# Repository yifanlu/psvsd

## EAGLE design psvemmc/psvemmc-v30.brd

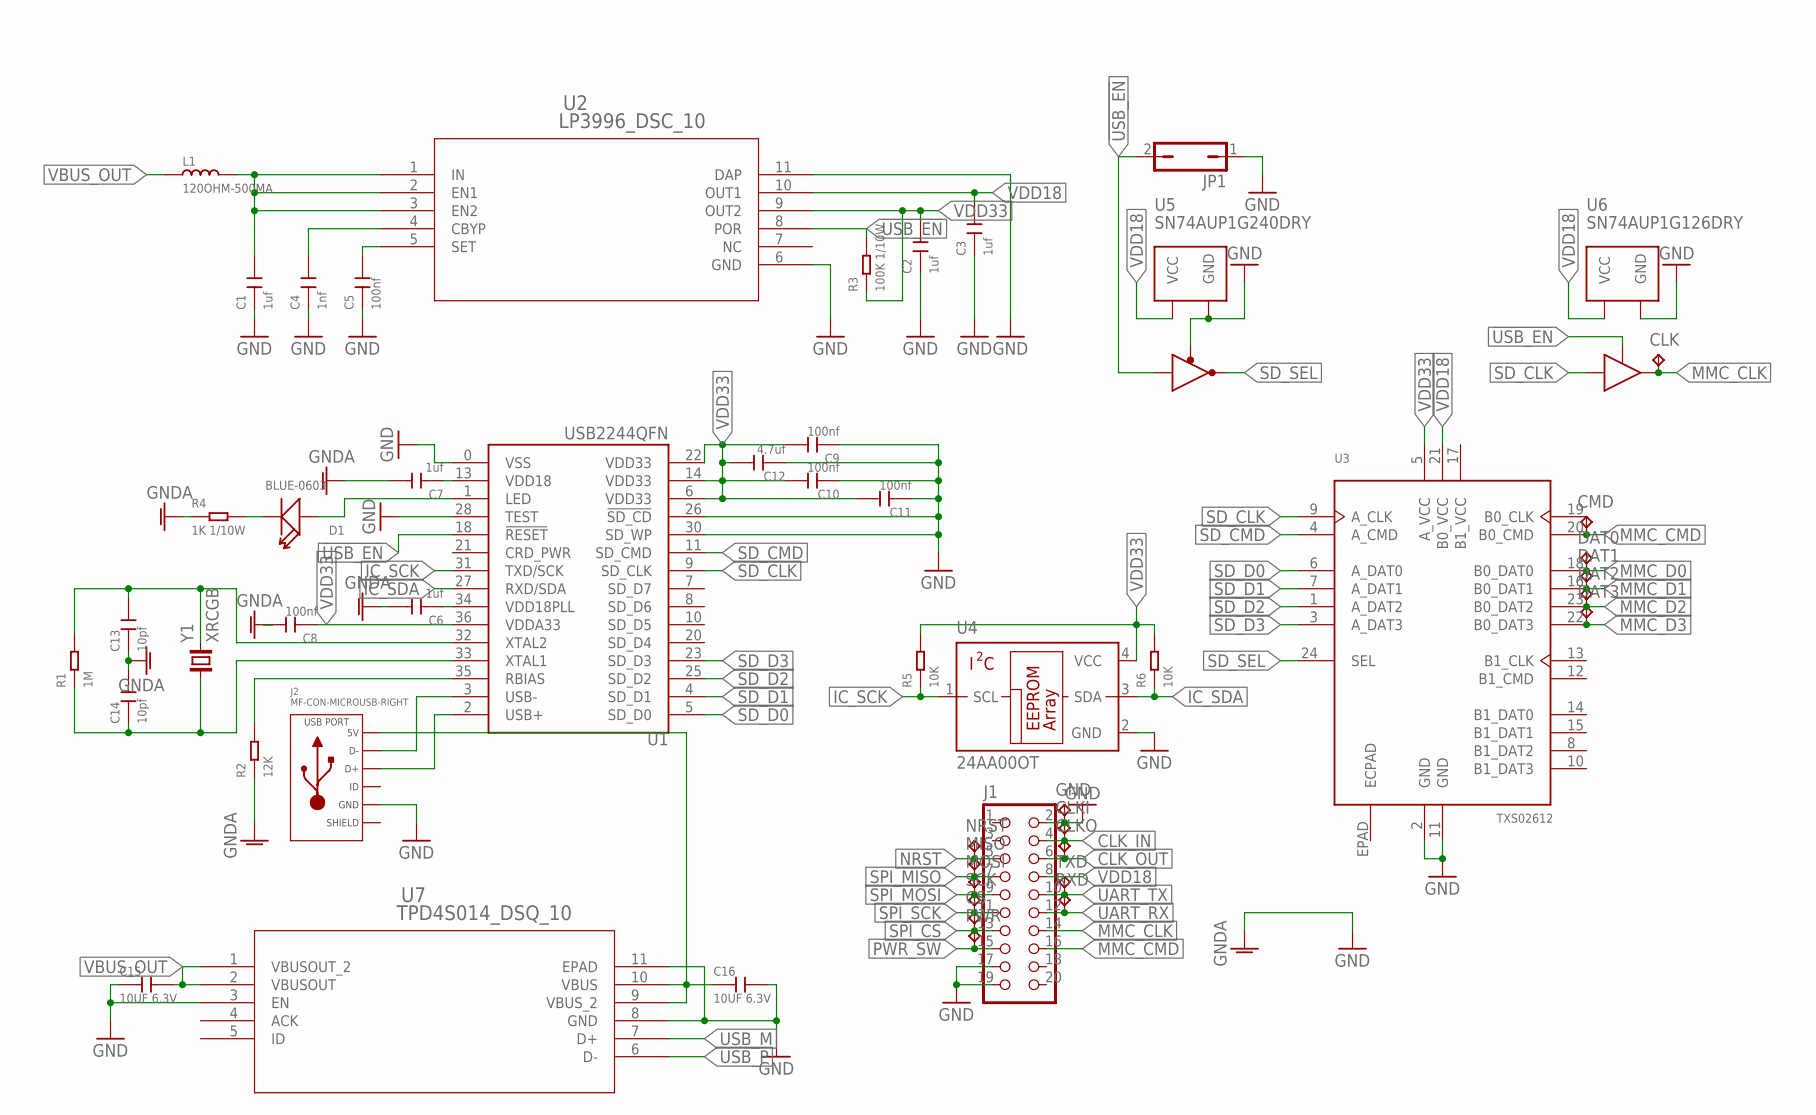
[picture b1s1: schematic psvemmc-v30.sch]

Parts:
C1, C2, C3, C6, C7: 1uf; C0603
C4: 1nf; C0603
C5, C8, C9, C10, C11: 100nf; C0603
C12: 4.7uf; C0603
C13, C14: 10pf; C0603
C15, C16: 10UF 6.3V; C0603
CLK: TPTP10R; TP10R
CLKI: TPTP10R; TP10R
CLKO: TPTP10R; TP10R
CMD: TPTP10R; TP10R
CS: TPTP10R; TP10R
D1: BLUE-0603; LED-0603
DAT0, DAT1, DAT2, DAT3: TPTP10R; TP10R
GND: TPTP10R; TP10R
J1: CON_HEADER_2X10-SHROUDED; PINSHRD_PTH_2X10
J2: MF-CON-MICROUSB-RIGHT; MICROUSB-RIGHT
JP1: JP1Q; JP1
L1: 120OHM-500MA; L0603
MISO: TPTP10R; TP10R
MOSI: TPTP10R; TP10R
NRST: TPTP10R; TP10R
PWR: TPTP10R; TP10R
R1: 1M; R0603
R2: 12K; R0603
R3: 100K 1/10W; R0603
R4: 1K 1/10W; R0603
R5, R6: 10K; R0603
RXD: TPTP10R; TP10R
SCK: TPTP10R; TP10R
TXD: TPTP10R; TP10R
U1: USB2244QFN; QFN36
U2: LP3996_DSC_10; SDA10A
U3: TXS02612; S-PWQFN-N24
U4: 24AA00OT; SOT23-5L
U5: SN74AUP1G240DRY; DRY6
U6: SN74AUP1G126DRY; DRY6
U7: TPD4S014_DSQ_10; DSQ10_1P5X0P9
Y1: XRCGB

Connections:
!USB_EN: JP1.2, R3.2, U1.18 (!RESET), U2.8 (POR), U5.2 (A), U6.1 (OE)
B1_VCC: U3.17 (B1_VCC)
CLK_IN: CLKI.TP, J1.4
CLK_OUT: CLKO.TP, J1.6
ECPAD: U3.EPAD (ECPAD)
GND: C1.1, C2.1, C3.1, C4.1, C5.1, C6.2, C7.2, C8.2, C9.1, C10.1, C11.1, C12.1, C13.1, C14.2, C15.1, C16.2, GND.TP, J1.2, J1.17, J1.19, J2.5 (GND), JP1.1, R2.1, R4.1, U1.0 (VSS), U1.26 (!SD_CD), U1.28 (TEST), U1.30 (SD_WP), U2.6 (GND), U2.11 (DAP), U3.2 (GND), U3.11 (GND), U4.2 (GND), U5.1 (!OE), U5.3 (GND), U6.3 (GND), U7.3 (EN), U7.8 (GND), U7.11 (EPAD)
IC_SCK: R5.1, U1.31 (TXD/SCK), U4.1 (SCL)
IC_SDA: R6.1, U1.27 (RXD/SDA), U4.3 (SDA)
LED: D1.+, U1.1 (LED)
LED_M: D1.-, R4.2
MMC_CLK: CLK.TP, J1.14, U6.4 (Y)
MMC_CMD: CMD.TP, J1.16, U3.20 (B0_CMD)
MMC_D0: DAT0.TP, U3.18 (B0_DAT0)
MMC_D1: DAT1.TP, U3.16 (B0_DAT1)
MMC_D2: DAT2.TP, U3.23 (B0_DAT2)
MMC_D3: DAT3.TP, U3.22 (B0_DAT3)
unnamed: C4.2, U2.4 (CBYP)
NRST: J1.5, NRST.TP
PWR_SW: J1.15, PWR.TP
RBIAS: R2.2, U1.35 (RBIAS)
SD_CLK: U1.9 (SD_CLK), U3.9 (A_CLK), U6.2 (A)
SD_CMD: U1.11 (SD_CMD), U3.4 (A_CMD)
SD_D0: U1.5 (SD_D0), U3.6 (A_DAT0)
SD_D1: U1.4 (SD_D1), U3.7 (A_DAT1)
SD_D2: U1.25 (SD_D2), U3.1 (A_DAT2)
SD_D3: U1.23 (SD_D3), U3.3 (A_DAT3)
SD_SEL: U3.24 (SEL), U5.4 (Y)
SET: C5.2, U2.5 (SET)
SLD: J2.S1 (SLD), J2.S2 (SLD), J2.S3 (SLD), J2.S4 (SLD), J2.S5 (SLD), J2.S6 (SLD)
SPI_CS: CS.TP, J1.13
SPI_MISO: J1.7, MISO.TP
SPI_MOSI: J1.9, MOSI.TP
SPI_SCK: J1.11, SCK.TP
UART_RX: J1.12, RXD.TP
UART_TX: J1.10, TXD.TP
USB_5V: C16.1, J2.1 (5V), U7.9 (VBUS_2), U7.10 (VBUS)
USB_M: J2.2 (D-), U1.3 (USB-), U7.7 (D+)
USB_P: J2.3 (D+), U1.2 (USB+), U7.6 (D-)
VBUS_OUT: C15.2, L1.1, U7.1 (VBUSOUT_2), U7.2 (VBUSOUT)
VDD5: C1.2, L1.2, U2.1 (IN), U2.2 (EN1), U2.3 (EN2)
VDD18: C3.2, J1.8, U2.10 (OUT1), U3.21 (B0_VCC), U5.6 (VCC), U6.6 (VCC)
VDD18_PLL: C6.1, U1.34 (VDD18PLL)
VDD18_USB: C7.1, U1.13 (VDD18)
VDD33: C2.2, C8.1, C9.2, C10.2, C11.2, C12.2, R3.1, R5.2, R6.2, U1.6 (VDD33), U1.14 (VDD33), U1.22 (VDD33), U1.36 (VDDA33), U2.9 (OUT2), U3.5 (A_VCC), U4.4 (VCC)
XTAL1: C14.1, R1.1, U1.33 (XTAL1), Y1.1
XTAL2: C13.2, R1.2, U1.32 (XTAL2), Y1.3 (2)

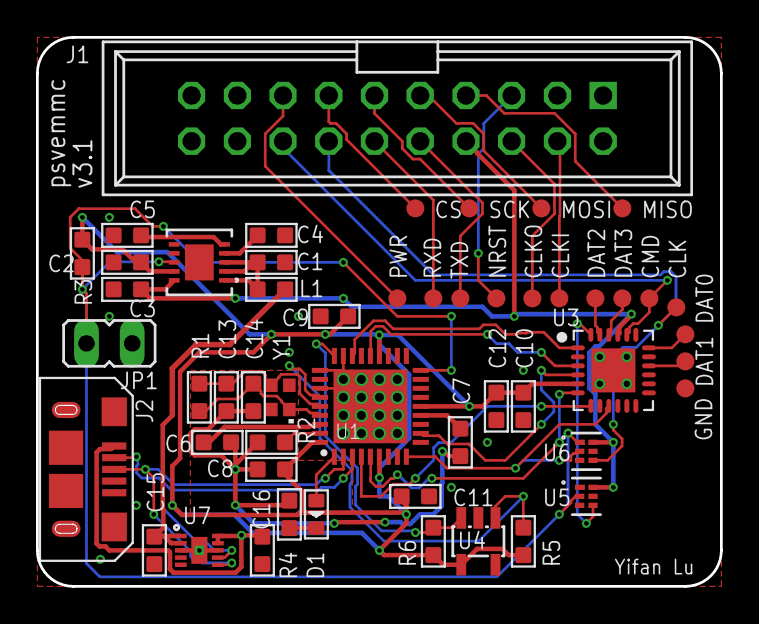
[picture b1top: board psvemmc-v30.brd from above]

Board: 2 copper layers, 38.0 x 30.5 mm, 52 parts (0 on the bottom side), 44 nets.

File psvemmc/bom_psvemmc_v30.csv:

Qty,Value,Device,Package,Parts
1,PINHD-2X5,Pin Header,2X05,JP1
1,100K,Resistor,0603,R3
5,100nF,Ceramic Capacitor,0603,"C5, C8, C9, C10, C11"
2,,Ferrite Bead,0603,"L1, L2"
1,12K,Resistor,0603,R2
1,1K,Resistor,0603,R4
1,1M,Resistor,0603,R1
1,10K,Resistor,0603,"R5, R6"
1,1nF,Ceramic Capacitor,0603,C4
5,1uF,Ceramic Capacitor Low ESR,0603,"C1, C2, C3, C6, C7"
1,4.7uF,Ceramic Capacitor Low ESR,0603,C12
2,10pF,Ceramic Capacitor,0603,"C13, C14"
2,10uF,Ceramic Capacitor,0603,"C15, C16"
1,BLUE,LED 0603,0603,D1
1,LP3996SD-1833/NOPB,"Texas Instruments LP3996 Dual LDO, 1.8V, 3.3V",WSON,U2
1,TXS02612RTWR,Texas Instruments TXS02612,RTW,U3
1,USB2244-AEZG-06,Microchip USB2244,QFN36,U1
1,XRCGB24M000F3N00R0,"Murata Hybrid Crystal, 24.000MHz, 30ppm, 6pF",XRCGB,Y1
1,10118193-0001LF,"FCI micro-USB port",,J2
1,24AA04T-I/OT,"Microchip 4K I2C EEPROM",SOT23-5,U4
1,SN74AUP1G240DRYR,"TI Low-Power Single Buffer/Driver with 3-State Output",SON,U5
1,SN74LVC1G125DRYR,"TI Low-Power Single Buffer/Driver with 3-State Output",SON,U6
1,TPD4S014DSQR,"TI USB Port Protection Device",WSON,U7

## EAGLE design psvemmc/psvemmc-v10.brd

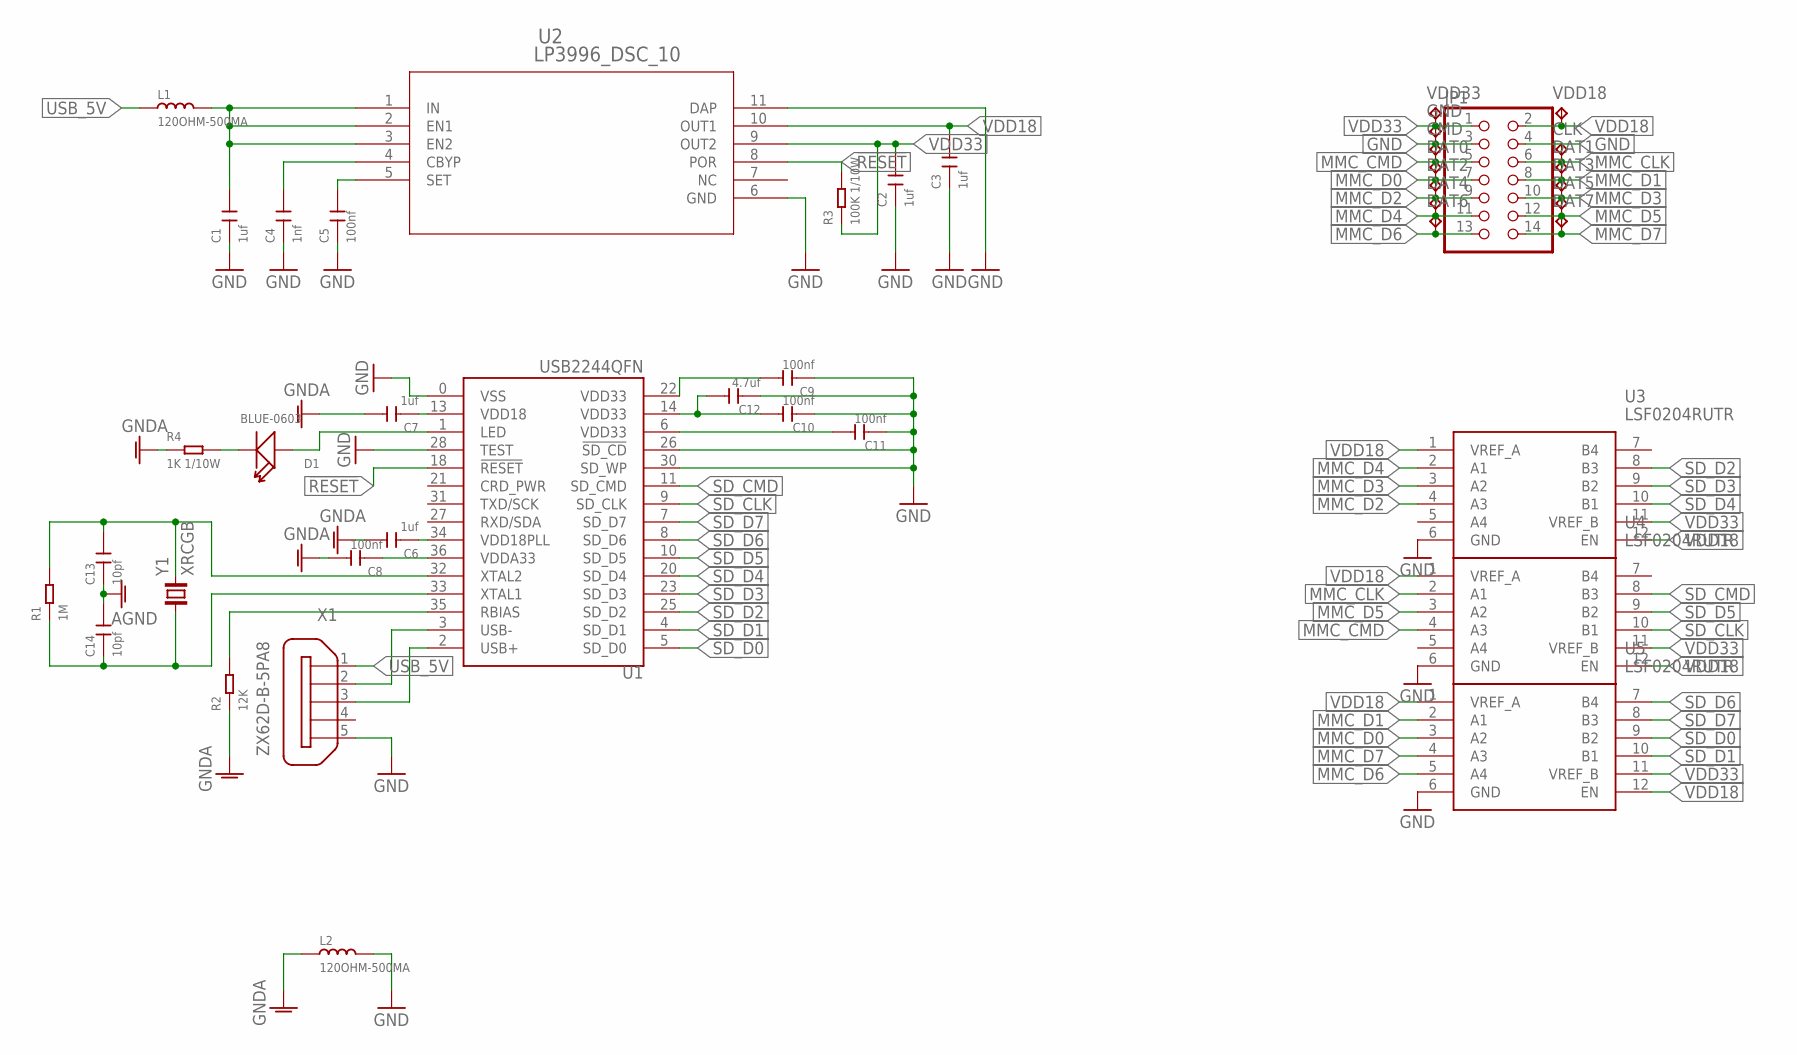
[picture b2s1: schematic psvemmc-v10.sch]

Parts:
C1, C2, C3, C6, C7: 1uf; C0603
C4: 1nf; C0603
C5, C8, C9, C10, C11: 100nf; C0603
C12: 4.7uf; C0603
C13, C14: 10pf; C0603
CLK: TPTP20SQ; TP20SQ
CMD: TPTP20SQ; TP20SQ
D1: BLUE-0603; LED-0603
DAT0, DAT1, DAT2, DAT3, DAT4, DAT5, DAT6, DAT7: TPTP20SQ; TP20SQ
GND: TPTP20SQ; TP20SQ
JP1: PINHD-2X7; 2X07
L1, L2: 120OHM-500MA; L0603
R1: 1M; R0603
R2: 12K; R0603
R3: 100K 1/10W; R0603
R4: 1K 1/10W; R0603
U1: USB2244QFN; QFN36
U2: LP3996_DSC_10; SDA10A
U3, U4, U5: LSF0204RUTR; RUT(R-PUQFN-N12)
VDD18, VDD33: TPTP20SQ; TP20SQ
X1: ZX62D-B-5PA8
Y1: XRCGB

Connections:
!RESET: R3.2, U1.18 (!RESET), U2.8 (POR)
GND: C1.1, C2.1, C3.1, C4.1, C5.1, C9.1, C10.1, C11.1, C12.1, GND.TP, JP1.3, JP1.4, L2.2, U1.0 (VSS), U1.26 (!SD_CD), U1.28 (TEST), U1.30 (SD_WP), U2.6 (GND), U2.11 (DAP), U3.6 (GND), U4.6 (GND), U5.6 (GND), X1.5
GNDA: C6.2, C7.2, C8.2, C13.1, C14.2, L2.1, R2.1, R4.1
LED: D1.+, U1.1 (LED)
LED_M: D1.-, R4.2
MMC_CLK: CLK.TP, JP1.6, U4.2 (A1)
MMC_CMD: CMD.TP, JP1.5, U4.4 (A3)
MMC_D0: DAT0.TP, JP1.7, U5.3 (A2)
MMC_D1: DAT1.TP, JP1.8, U5.2 (A1)
MMC_D2: DAT2.TP, JP1.9, U3.4 (A3)
MMC_D3: DAT3.TP, JP1.10, U3.3 (A2)
MMC_D4: DAT4.TP, JP1.11, U3.2 (A1)
MMC_D5: DAT5.TP, JP1.12, U4.3 (A2)
MMC_D6: DAT6.TP, JP1.13, U5.5 (A4)
MMC_D7: DAT7.TP, JP1.14, U5.4 (A3)
unnamed: C4.2, U2.4 (CBYP)
RBIAS: R2.2, U1.35 (RBIAS)
SD_CLK: U1.9 (SD_CLK), U4.10 (B1)
SD_CMD: U1.11 (SD_CMD), U4.8 (B3)
SD_D0: U1.5 (SD_D0), U5.9 (B2)
SD_D1: U1.4 (SD_D1), U5.10 (B1)
SD_D2: U1.25 (SD_D2), U3.8 (B3)
SD_D3: U1.23 (SD_D3), U3.9 (B2)
SD_D4: U1.20 (SD_D4), U3.10 (B1)
SD_D5: U1.10 (SD_D5), U4.9 (B2)
SD_D6: U1.8 (SD_D6), U5.7 (B4)
SD_D7: U1.7 (SD_D7), U5.8 (B3)
SET: C5.2, U2.5 (SET)
USB_5V: L1.1, X1.1
USB_M: U1.3 (USB-), X1.2
USB_P: U1.2 (USB+), X1.3
VDD5: C1.2, L1.2, U2.1 (IN), U2.2 (EN1), U2.3 (EN2)
VDD18: C3.2, JP1.2, U2.10 (OUT1), U3.1 (VREF_A), U3.12 (EN), U4.1 (VREF_A), U4.12 (EN), U5.1 (VREF_A), U5.12 (EN), VDD18.TP
VDD18_PLL: C6.1, U1.34 (VDD18PLL)
VDD18_USB: C7.1, U1.13 (VDD18)
VDD33: C2.2, C8.1, C9.2, C10.2, C11.2, C12.2, JP1.1, R3.1, U1.6 (VDD33), U1.14 (VDD33), U1.22 (VDD33), U1.36 (VDDA33), U2.9 (OUT2), U3.11 (VREF_B), U4.11 (VREF_B), U5.11 (VREF_B), VDD33.TP
XTAL1: C14.1, R1.1, U1.33 (XTAL1), Y1.1
XTAL2: C13.2, R1.2, U1.32 (XTAL2), Y1.3 (2)

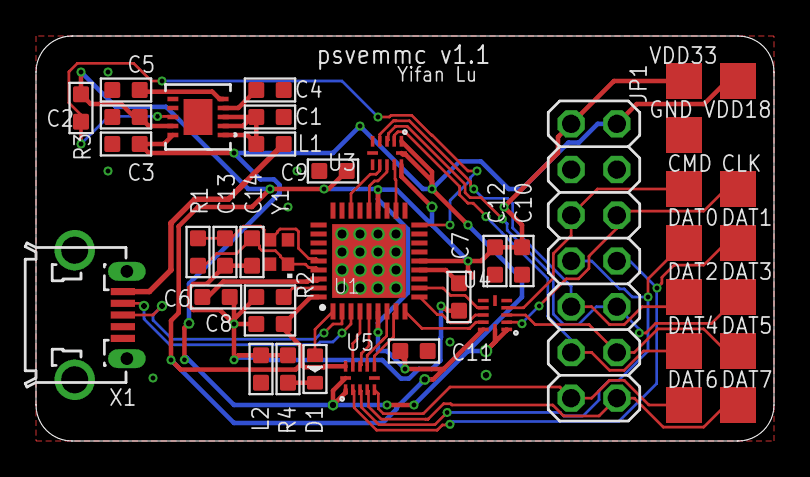
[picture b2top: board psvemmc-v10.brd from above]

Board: 2 copper layers, 41.0 x 22.5 mm, 42 parts (0 on the bottom side), 38 nets.

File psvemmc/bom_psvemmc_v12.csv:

Qty,Value,Device,Package,Parts
1,PINHD-2X5,Pin Header,2X05,JP1
1,100K,Resistor,0603,R3
5,100nF,Ceramic Capacitor,0603,"C5, C8, C9, C10, C11"
2,,Ferrite Bead,0603,"L1, L2"
1,12K,Resistor,0603,R2
1,1K,Resistor,0603,R4
1,1M,Resistor,0603,R1
1,1nF,Ceramic Capacitor,0603,C4
5,1uF,Ceramic Capacitor Low ESR,0603,"C1, C2, C3, C6, C7"
1,4.7uF,Ceramic Capacitor Low ESR,0603,C12
2,10pF,Ceramic Capacitor,0603,"C13, C14"
1,BLUE,LED 0603,0603,D1
1,LP3996SD-1833/NOPB,"Texas Instruments LP3996 Dual LDO, 1.8V, 3.3V",WSON,U2
1,TXS02612RTWR,Texas Instruments TXS02612,RTW,U3
1,USB2244-AEZG-06,Microchip USB2244,QFN36,U1
1,XRCGB24M000F3N00R0,"Murata Hybrid Crystal, 24.000MHz, 30ppm, 6pF",XRCGB,Y1
1,,"Micro USB Type AB receptacle, through hole",,X1

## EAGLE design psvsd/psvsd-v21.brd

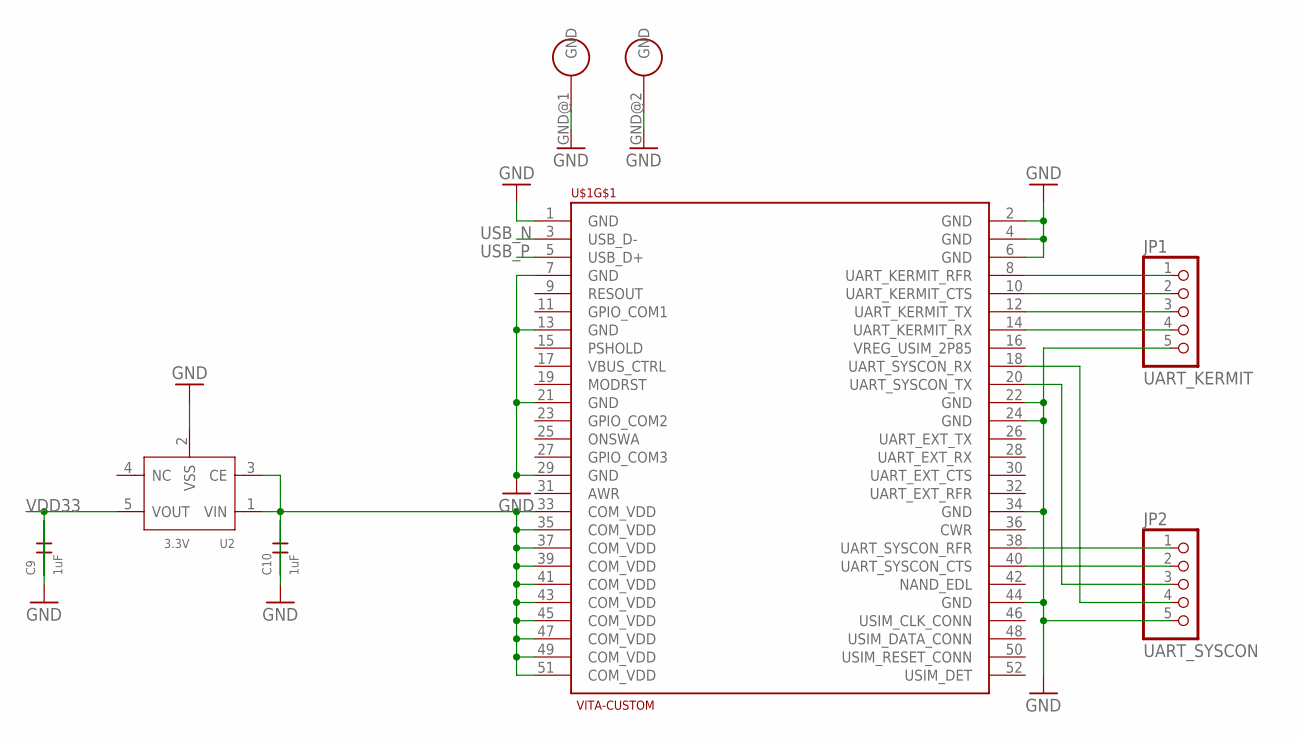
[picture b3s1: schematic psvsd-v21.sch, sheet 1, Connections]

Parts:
C9, C10: 1uF; C0603
JP1: UART_KERMIT; 1X05
JP2: UART_SYSCON; 1X05
U2: 3.3V; SOT-23-5
U$1: VITA-CUSTOM; VITA-MINI-PCI-E

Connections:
GND: C9.2, C10.2, JP1.5, JP2.5, U2.2 (VSS), U$1.1 (GND), U$1.2 (GND), U$1.4 (GND), U$1.6 (GND), U$1.7 (GND), U$1.13 (GND), U$1.21 (GND), U$1.22 (GND), U$1.24 (GND), U$1.29 (GND), U$1.34 (GND), U$1.44 (GND), U$1.GND@1 (GND), U$1.GND@2 (GND); also elsewhere on the board
UART_KERMIT_CTS: JP1.2, U$1.10 (UART_KERMIT_CTS)
UART_KERMIT_RFR: JP1.1, U$1.8 (UART_KERMIT_RFR)
UART_KERMIT_RX: JP1.4, U$1.14 (UART_KERMIT_RX)
UART_KERMIT_TX: JP1.3, U$1.12 (UART_KERMIT_TX)
UART_SYSCON_CTS: JP2.2, U$1.40 (UART_SYSCON_CTS)
UART_SYSCON_RFR: JP2.1, U$1.38 (UART_SYSCON_RFR)
UART_SYSCON_RX: JP2.4, U$1.18 (UART_SYSCON_RX)
UART_SYSCON_TX: JP2.3, U$1.20 (UART_SYSCON_TX)
USB_N: U$1.3 (USB_D-); also elsewhere on the board
USB_P: U$1.5 (USB_D+); also elsewhere on the board
VDD: C10.1, U2.1 (VIN), U2.3 (CE), U$1.33 (COM_VDD), U$1.35 (COM_VDD), U$1.37 (COM_VDD), U$1.39 (COM_VDD), U$1.41 (COM_VDD), U$1.43 (COM_VDD), U$1.45 (COM_VDD), U$1.47 (COM_VDD), U$1.49 (COM_VDD), U$1.51 (COM_VDD)
VDD33: C9.1, U2.5 (VOUT); also elsewhere on the board

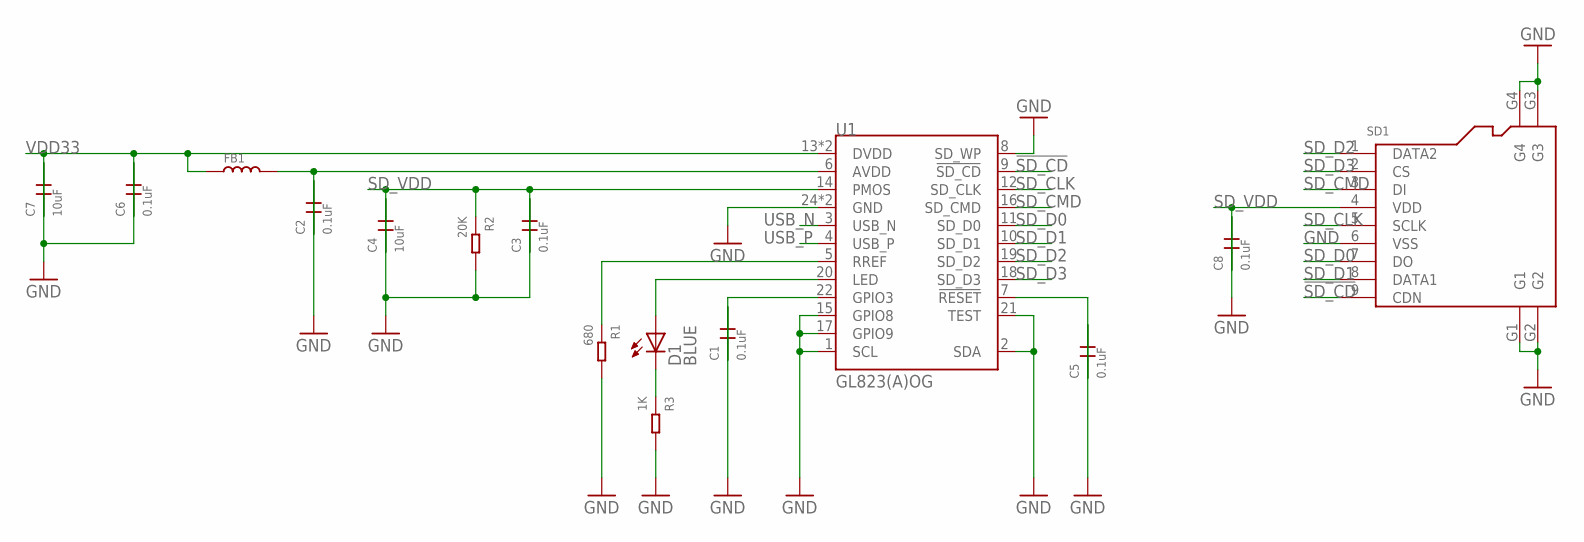
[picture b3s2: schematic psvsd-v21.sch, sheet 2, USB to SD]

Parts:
C1, C2, C3, C5, C6, C8: 0.1uF; C0603
C4, C7: 10uF; C0603
D1: BLUE; CHIP-LED0603
FB1: SMD-FERRITE-BEAD-2500R-50MA(0603); L0603
R1: 680; R0603
R2: 20K; R0603
R3: 1K; R0603
SD1: MICRO-SD-CARD-SOCKET-9P(ST-TF-003A); MICRO-SD9+4P-SMD-16.1X14.5X1.85MM
U1: GL823(A)OG; QFN-24

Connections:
!RESET: C5.1, U1.7 (!RESET)
!SD_CD: SD1.9 (CDN), U1.9 (!SD_CD)
AVDD33: C2.1, FB1.2, U1.6 (AVDD)
GND: C1.2, C2.2, C3.2, C4.2, C5.2, C6.2, C7.2, C8.2, R1.2, R2.2, R3.2, SD1.6 (VSS), SD1.G1, SD1.G2, SD1.G3, SD1.G4, U1.1 (SCL), U1.2 (SDA), U1.8 (SD_WP), U1.15 (GPIO8), U1.17 (GPIO9), U1.21 (TEST), U1.24 (GND), U1.25 (GND); also elsewhere on the board
GPIO3: C1.1, U1.22 (GPIO3)
LED: D1.A, U1.20 (LED)
LED_N: D1.C, R3.1
RREF: R1.1, U1.5 (RREF)
SD_CLK: SD1.5 (SCLK), U1.12 (SD_CLK)
SD_CMD: SD1.3 (DI), U1.16 (SD_CMD)
SD_D0: SD1.7 (DO), U1.11 (SD_D0)
SD_D1: SD1.8 (DATA1), U1.10 (SD_D1)
SD_D2: SD1.1 (DATA2), U1.19 (SD_D2)
SD_D3: SD1.2 (CS), U1.18 (SD_D3)
SD_VDD: C3.1, C4.1, C8.1, R2.1, SD1.4 (VDD), U1.14 (PMOS)
USB_N: U1.3 (USB_N); also elsewhere on the board
USB_P: U1.4 (USB_P); also elsewhere on the board
VDD33: C6.1, C7.1, FB1.1, U1.13 (DVDD), U1.23 (DVDD); also elsewhere on the board

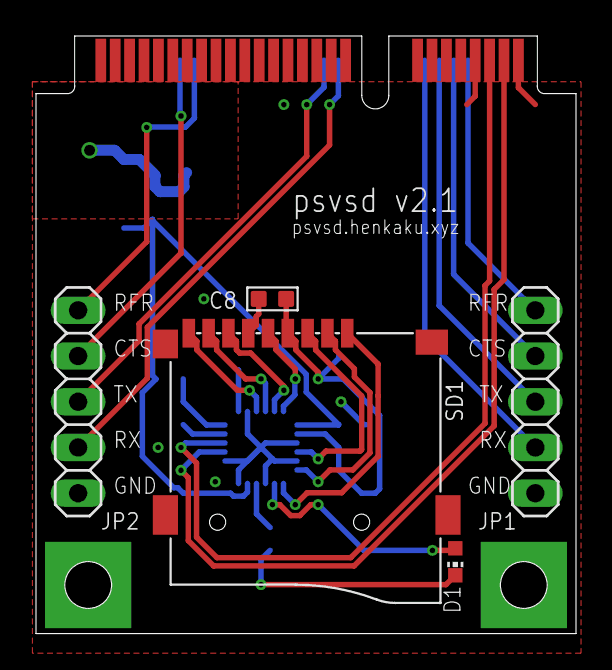
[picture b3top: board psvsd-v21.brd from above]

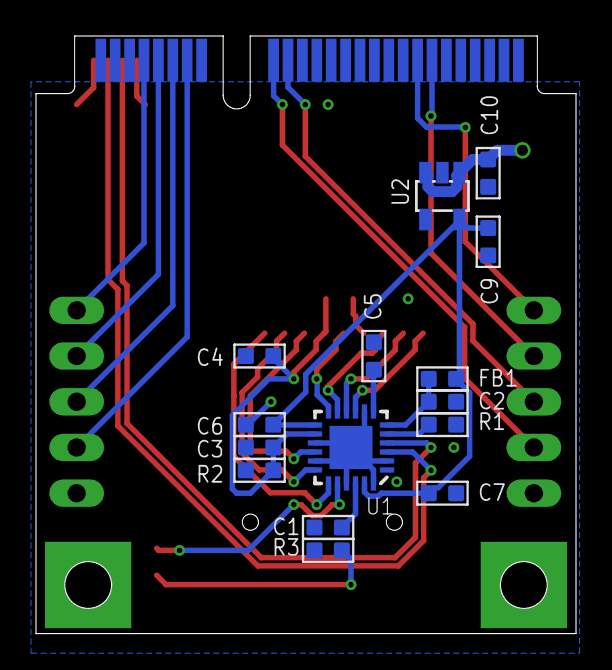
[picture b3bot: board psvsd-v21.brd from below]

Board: 2 copper layers, 30.0 x 33.2 mm, 21 parts (15 on the bottom side), 27 nets.

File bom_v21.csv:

Qty,Reference,Description,Manufacturer,Part,Notes
6,"C1,C2,C3,C5,C6,C8","Capacitor, 0.1uF, 0603",Yageo,CC0603KRX7R9BB104,
2,"C4,C7","Capacitor, 10uF, 0603",Murata,GRM188R60J106ME47D,
2,"C9,C10","Capacitor, 1.0uF, 0603",Yageo,CC0603KRX7R8BB105,
1,FB1,"Ferrite Bead, 120 Ohm @ 100MHz, 0603",Murata,BLM18TG121TN1D,
1,SD1,SMD Micro SD Card Socket,Best,TF-01,
2,"JP1,JP2","Pin Headers 0.1” spacing, 5",,,Only fill if needed
1,R1,"Resistor, 680, 0603",Yageo,RC0603JR-07680RL,
1,R2,"Resistor, 20K, 0603",Yageo,RC0603FR-0720KL,
1,R3,"Resistor, 1K, 0603",Yageo,RC0603JR-071KL,
1,D1,"LED Blue, 3.2V, 20mA, 0603",Everlight,19-217-BHC-ZL1M2RY-3T,
1,U2,"LDO 3.3V, 200mA",Micrel,MIC5504-3.3YM5-TR,
1,U1,GL823 3.3V QFN24,Genesys,GL823,

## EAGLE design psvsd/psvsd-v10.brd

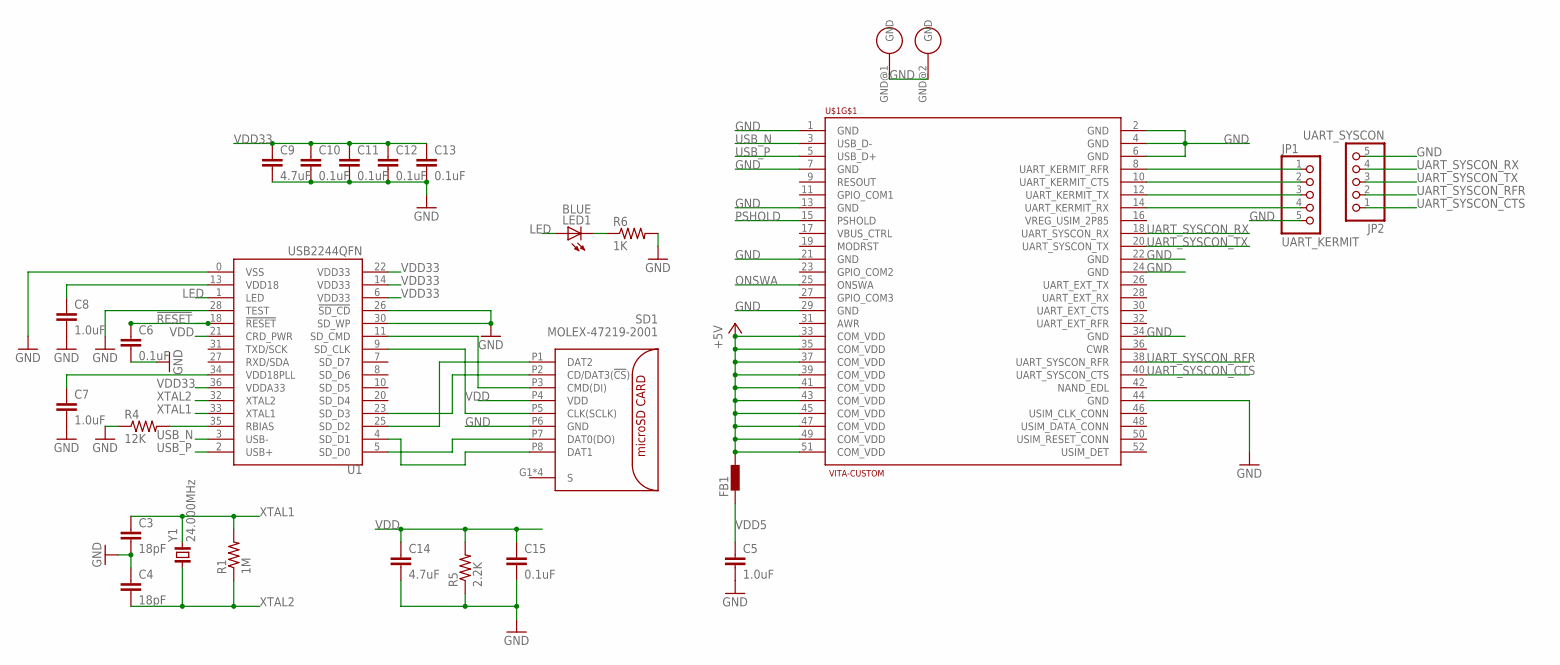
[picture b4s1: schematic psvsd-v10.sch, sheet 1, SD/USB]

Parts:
C3, C4: 18pF; C0402
C5, C7, C8: 1.0uF; C0603
C6, C10, C11, C12, C13, C15: 0.1uF; C0402
C9, C14: 4.7uF; C0603
FB1: BLM15HB121SN1; 0402
JP1: UART_KERMIT; 1X05
JP2: UART_SYSCON; 1X05
LED1: BLUE; SML0603
R1: 1M; R0603
R4: 12K; R0603
R5: 2.2K; R0603
R6: 1K; R0603
SD1: MOLEX-47219-2001; MOLEX:47219-2001
U1: USB2244QFN; QFN36
U$1: VITA-CUSTOM; VITA-MINI-PCI-E
Y1: 24.000MHz; XRCGB

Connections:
!RESET: C6.1, U1.18 (!RESET); also elsewhere on the board
+5V: FB1.2, U$1.33 (COM_VDD), U$1.35 (COM_VDD), U$1.37 (COM_VDD), U$1.39 (COM_VDD), U$1.41 (COM_VDD), U$1.43 (COM_VDD), U$1.45 (COM_VDD), U$1.47 (COM_VDD), U$1.49 (COM_VDD), U$1.51 (COM_VDD)
GND: C3.2, C4.1, C5.2, C6.2, C7.2, C8.2, C9.2, C10.2, C11.2, C12.2, C13.2, C14.2, C15.2, JP1.5, JP2.5, R4.1, R5.1, R6.2, SD1.P6 (GND), U1.0 (VSS), U1.26 (!SD_CD), U1.28 (TEST), U1.30 (SD_WP), U$1.1 (GND), U$1.2 (GND), U$1.4 (GND), U$1.6 (GND), U$1.7 (GND), U$1.13 (GND), U$1.21 (GND), U$1.22 (GND), U$1.24 (GND), U$1.29 (GND), U$1.34 (GND), U$1.44 (GND), U$1.GND@1 (GND), U$1.GND@2 (GND); also elsewhere on the board
LED: LED1.A, U1.1 (LED)
unnamed: LED1.C, R6.1
ONSWA: U$1.25 (ONSWA); also elsewhere on the board
PSHOLD: U$1.15 (PSHOLD); also elsewhere on the board
RBIAS: R4.2, U1.35 (RBIAS)
SD_CLK: SD1.P5 (CLK(SCLK)), U1.9 (SD_CLK)
SD_CMD: SD1.P3 (CMD(DI)), U1.11 (SD_CMD)
SD_D0: SD1.P7 (DAT0(DO)), U1.5 (SD_D0)
SD_D1: SD1.P8 (DAT1), U1.4 (SD_D1)
SD_D2: SD1.P1 (DAT2), U1.25 (SD_D2)
SD_D3: SD1.P2 (CD/DAT3(!CS!)), U1.23 (SD_D3)
UART_KERMIT_CTS: JP1.2, U$1.10 (UART_KERMIT_CTS)
UART_KERMIT_RFR: JP1.1, U$1.8 (UART_KERMIT_RFR)
UART_KERMIT_RX: JP1.4, U$1.14 (UART_KERMIT_RX)
UART_KERMIT_TX: JP1.3, U$1.12 (UART_KERMIT_TX)
UART_SYSCON_CTS: JP2.1, U$1.40 (UART_SYSCON_CTS)
UART_SYSCON_RFR: JP2.2, U$1.38 (UART_SYSCON_RFR)
UART_SYSCON_RX: JP2.4, U$1.18 (UART_SYSCON_RX)
UART_SYSCON_TX: JP2.3, U$1.20 (UART_SYSCON_TX)
USBVDD18: C8.1, U1.13 (VDD18)
USBVDD18PLL: C7.1, U1.34 (VDD18PLL)
USB_N: U1.3 (USB-), U$1.3 (USB_D-)
USB_P: U1.2 (USB+), U$1.5 (USB_D+)
VDD: C14.1, C15.1, R5.2, SD1.P4 (VDD), U1.21 (CRD_PWR)
VDD5: C5.1, FB1.1; also elsewhere on the board
VDD33: C9.1, C10.1, C11.1, C12.1, C13.1, U1.6 (VDD33), U1.14 (VDD33), U1.22 (VDD33), U1.36 (VDDA33); also elsewhere on the board
XTAL1: C3.1, R1.2, U1.33 (XTAL1), Y1.3 (2)
XTAL2: C4.2, R1.1, U1.32 (XTAL2), Y1.1

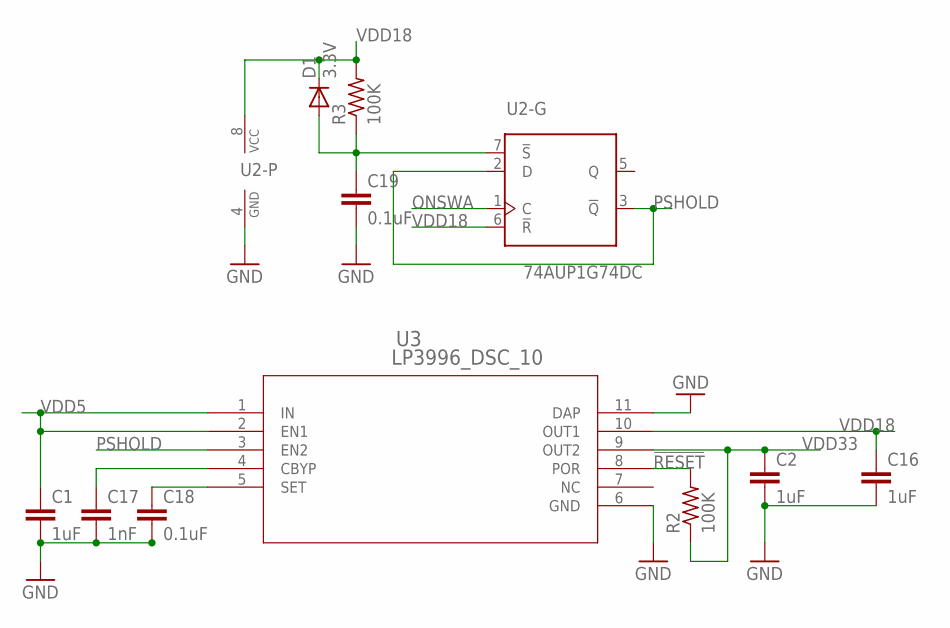
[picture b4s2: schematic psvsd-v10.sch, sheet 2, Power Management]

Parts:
C1, C2, C16: 1uF; C0603
C17: 1nF; C0402
C18, C19: 0.1uF; C0402
D1: 3.3V; SOD523
R2, R3: 100K; R0603
U2: 74AUP1G74DC; SOT765
U3: LP3996_DSC_10; SDA10A

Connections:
!RESET: R2.2, U3.8 (POR); also elsewhere on the board
!S: C19.1, D1.A, R3.1, U2.7 (!S)
CBYP: C17.1, U3.4 (CBYP)
CSET: C18.1, U3.5 (SET)
GND: C1.2, C2.2, C16.2, C17.2, C18.2, C19.2, U2.4 (GND), U3.6 (GND), U3.11 (DAP); also elsewhere on the board
ONSWA: U2.1 (C); also elsewhere on the board
PSHOLD: U2.2 (D), U2.3 (!Q), U3.3 (EN2); also elsewhere on the board
VDD5: C1.1, U3.1 (IN), U3.2 (EN1); also elsewhere on the board
VDD18: C16.1, D1.C, R3.2, U2.6 (!R), U2.8 (VCC), U3.10 (OUT1)
VDD33: C2.1, R2.1, U3.9 (OUT2); also elsewhere on the board

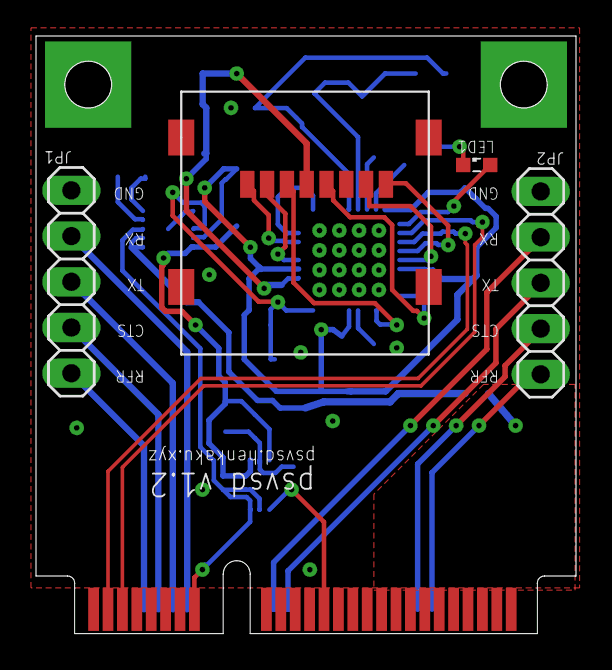
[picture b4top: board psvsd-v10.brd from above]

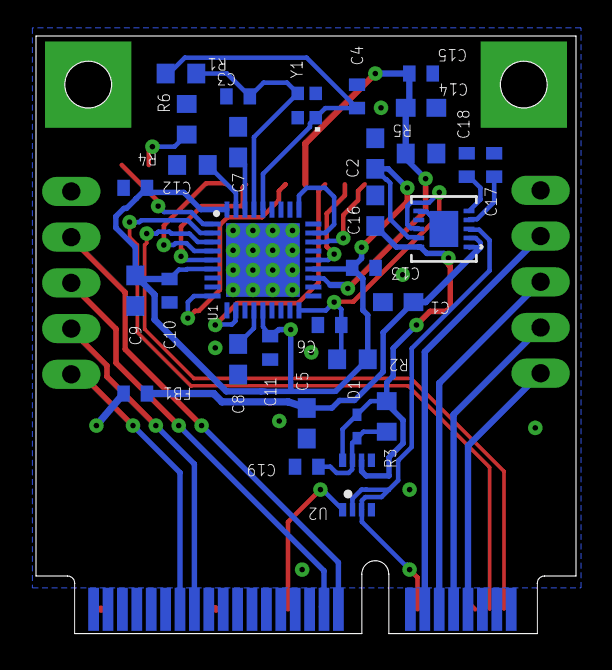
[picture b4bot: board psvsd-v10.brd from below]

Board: 2 copper layers, 30.0 x 33.2 mm, 36 parts (31 on the bottom side), 35 nets.

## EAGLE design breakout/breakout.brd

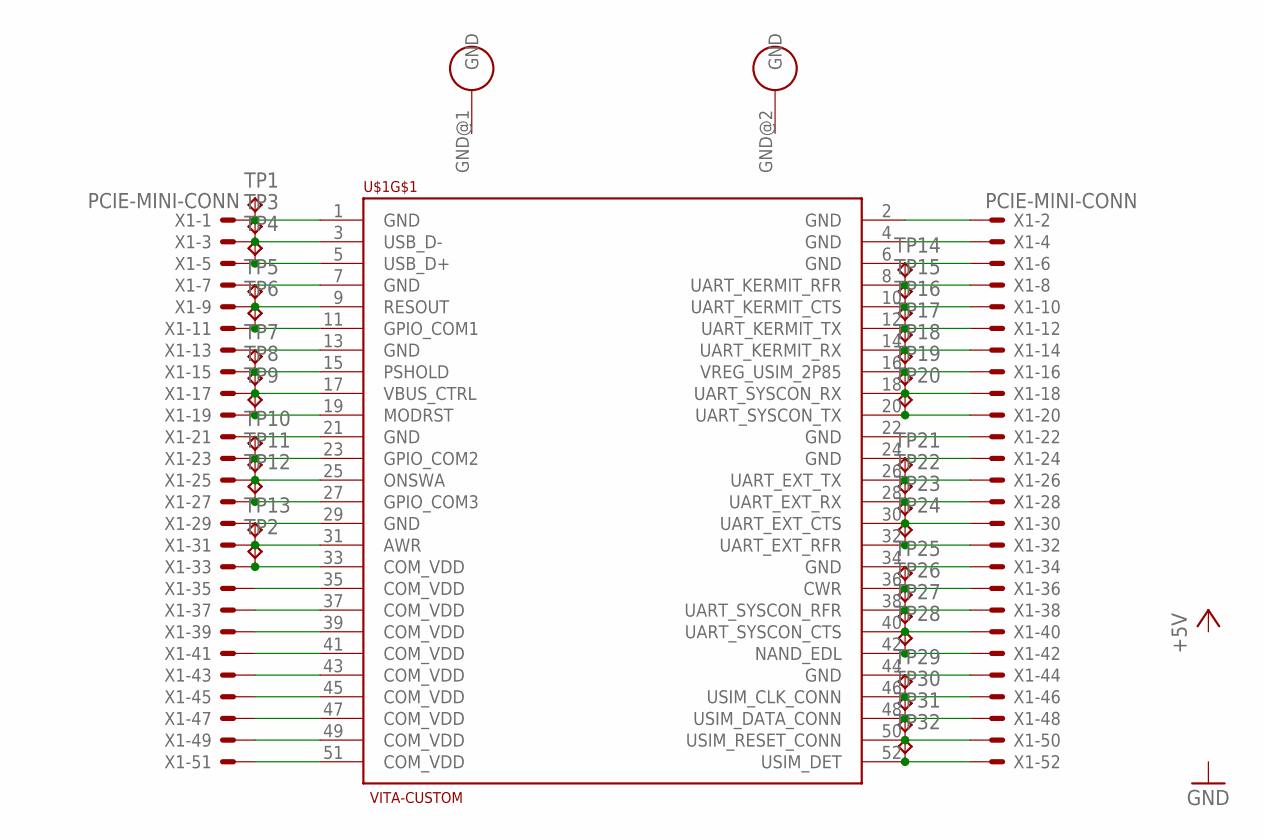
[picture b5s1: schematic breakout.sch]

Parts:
TP1, TP2, TP3, TP4, TP5, TP6, TP7, TP8, TP9, TP10, TP11, TP12, TP13, TP14, TP15, TP16, TP17, TP18, TP19, TP20, TP21, TP22, TP23, TP24, TP25, TP26, TP27, TP28, TP29, TP30, TP31, TP32: TPTP20R; TP20R
U$1: VITA-CUSTOM; VITA-MINI-PCI-E
X1: PCIE-MINI-CONN

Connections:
+5V: TP2.TP, U$1.33 (COM_VDD), U$1.35 (COM_VDD), U$1.37 (COM_VDD), U$1.39 (COM_VDD), U$1.41 (COM_VDD), U$1.43 (COM_VDD), U$1.45 (COM_VDD), U$1.47 (COM_VDD), U$1.49 (COM_VDD), U$1.51 (COM_VDD), X1.33, X1.35, X1.37, X1.39, X1.41, X1.43, X1.45, X1.47, X1.49, X1.51
AWR: TP13.TP, U$1.31 (AWR), X1.31
CWR: TP25.TP, U$1.36 (CWR), X1.36
GND: TP1.TP, U$1.1 (GND), U$1.2 (GND), U$1.4 (GND), U$1.6 (GND), U$1.7 (GND), U$1.13 (GND), U$1.21 (GND), U$1.22 (GND), U$1.24 (GND), U$1.29 (GND), U$1.34 (GND), U$1.44 (GND), U$1.GND@1 (GND), U$1.GND@2 (GND), X1.1, X1.2, X1.4, X1.6, X1.7, X1.13, X1.21, X1.22, X1.24, X1.29, X1.34, X1.44
GPIO_COM1: TP6.TP, U$1.11 (GPIO_COM1), X1.11
GPIO_COM2: TP10.TP, U$1.23 (GPIO_COM2), X1.23
GPIO_COM3: TP12.TP, U$1.27 (GPIO_COM3), X1.27
MODRST: TP9.TP, U$1.19 (MODRST), X1.19
NAND_EDL: TP28.TP, U$1.42 (NAND_EDL), X1.42
ONSWA: TP11.TP, U$1.25 (ONSWA), X1.25
PSHOLD: TP7.TP, U$1.15 (PSHOLD), X1.15
RESOUT: TP5.TP, U$1.9 (RESOUT), X1.9
UART_EXT_CTS: TP23.TP, U$1.30 (UART_EXT_CTS), X1.30
UART_EXT_RFR: TP24.TP, U$1.32 (UART_EXT_RFR), X1.32
UART_EXT_RX: TP22.TP, U$1.28 (UART_EXT_RX), X1.28
UART_EXT_TX: TP21.TP, U$1.26 (UART_EXT_TX), X1.26
UART_KERMIT_CTS: TP15.TP, U$1.10 (UART_KERMIT_CTS), X1.10
UART_KERMIT_RFR: TP14.TP, U$1.8 (UART_KERMIT_RFR), X1.8
UART_KERMIT_RX: TP17.TP, U$1.14 (UART_KERMIT_RX), X1.14
UART_KERMIT_TX: TP16.TP, U$1.12 (UART_KERMIT_TX), X1.12
UART_SYSCON_CTS: TP27.TP, U$1.40 (UART_SYSCON_CTS), X1.40
UART_SYSCON_RFR: TP26.TP, U$1.38 (UART_SYSCON_RFR), X1.38
UART_SYSCON_RX: TP19.TP, U$1.18 (UART_SYSCON_RX), X1.18
UART_SYSCON_TX: TP20.TP, U$1.20 (UART_SYSCON_TX), X1.20
USB_N: TP3.TP, U$1.3 (USB_D-), X1.3
USB_P: TP4.TP, U$1.5 (USB_D+), X1.5
USIM_CLK_CONN: TP29.TP, U$1.46 (USIM_CLK_CONN), X1.46
USIM_DATA_CONN: TP30.TP, U$1.48 (USIM_DATA_CONN), X1.48
USIM_DET: TP32.TP, U$1.52 (USIM_DET), X1.52
USIM_RESET_CONN: TP31.TP, U$1.50 (USIM_RESET_CONN), X1.50
VBUS_CTRL: TP8.TP, U$1.17 (VBUS_CTRL), X1.17
VREG_USIM_2P85: TP18.TP, U$1.16 (VREG_USIM_2P85), X1.16

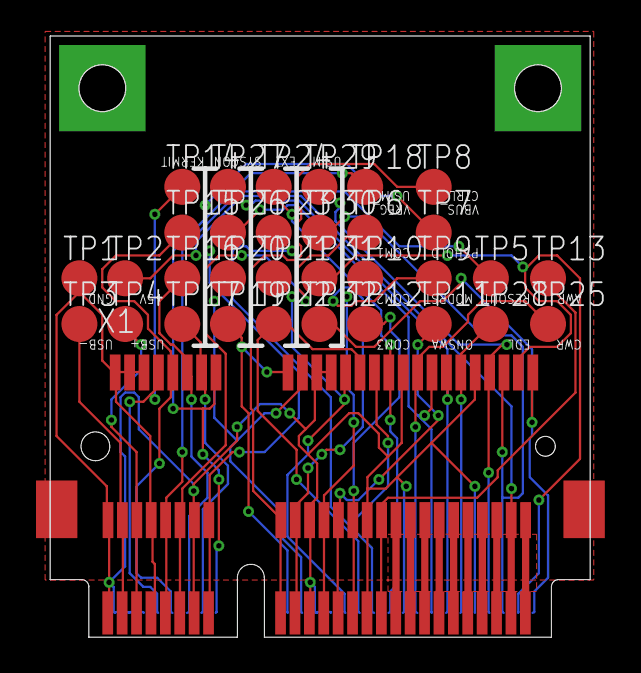
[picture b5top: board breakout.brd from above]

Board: 2 copper layers, 30.0 x 33.4 mm, 34 parts (0 on the bottom side), 32 nets.

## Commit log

2017-04-21 Initial commit.
2017-04-25 DRC fixes
2017-04-25 More cleanups
2017-04-25 Fixed dimensions
2017-04-25 Name/value layout in bottom layer
2017-04-25 Added forgotten tStop layer to USB2244 chip
2017-04-25 Moved some labels away from vias
2017-04-25 Added BOM
2017-04-26 Added breakout board
2017-04-26 Removed molex mark from silkscreen
2017-04-26 Better routing of the +5V pins to handle large currents
2017-04-26 Corrected wrong pins for USB+/USB-
2017-04-26 Fix incorrect signal in breakout board
2017-04-26 Fixed USB+/USB- signal in psvsd
2017-04-26 Fixed DRC for new USB lines placement
2017-04-27 Added new hinge-type microsd connector
2017-05-18 Added LED indicator
2017-05-19 Added Vita PCIe form factor
2017-05-19 Updated board to be right size
2017-05-19 Really size the vita card correctly now
2017-05-19 Resize both boards
2017-05-19 Shifted all components up in the new space
2017-05-19 Extended ground plane on top layer to even electric properties
2017-05-20 Replaced microSD connector with cheaper part
2017-05-20 Added value for LED
2017-05-20 Removed unneedeed lbr for hinge type molex connector
2017-05-24 Moved some labels in the silkscreen to prevent being cut off
2017-05-26 Moved two GND pin routing out of the flag since it is discouraged
2017-05-26 Enhanced heat sink under chip
2017-05-26 Added a power plane on top to dissipate the many +5V inputs
2017-05-27 Added MEM2051 part that will be used
2017-05-27 Reconnected ground planes
2017-05-27 Wrong silkscreen layer
2017-05-27 Changed RC circuit for reset to be tolerant of 4.0V
2017-06-01 Updated dimension size, off by 0.2mm
2017-06-01 Added license
2017-06-11 Moved some labels around in silkscreen
2017-06-18 Removed drill through pad because excess solder shorting sd socket pins
2017-06-22 Removed old LDO and reset circuit. Added new power efficient POR circuit & dual channel LDO
2017-06-22 Layout for PM circuit
2017-06-22 Changed to cheaper molex slot
2017-06-22 Routed new layout
2017-06-22 Placed labels for new components
2017-06-22 Forgot to rotate a label
2017-06-22 Changed crystal
2017-06-22 Updated BOM finishing new design. Resolves #2
2017-06-25 Added v2.0 design
2017-06-26 Placed labels in new design
2017-06-26 Added molecule logo to new design
2017-06-26 Added BOM for v2 design
2017-06-26 Added USB trace clearance recommendations from GL823 design docs
2017-07-08 Changed bypass value for DVDD2 and added a new ferrite bead to AVDD
2017-07-11 Added RC delay to power circuit
2017-07-11 Added v2.1 design without power circuit
2017-07-12 Finished silkscreen and added BOM for v2.1 design
2017-07-31 Set theme jekyll-theme-cayman
2017-07-31 Create CNAME
2017-08-17 Fixed problem where shield is not grounded
2017-09-16 Updated image
2017-12-02 Added SphereSolid seller
2018-03-02 Added psvemmc
2018-03-08 Added BOM for psvemmc
2018-03-15 psvemmc v1.1: fixed missing caps for crystal and fixed direction of translator
2018-04-02 psvemmc v1.2: changed broken TTL translater
2018-04-02 psvemmc v1.2: unified drill sizes, added thermal vias to TTL translation IC
2018-07-09 Added psvemmc v2.0
2018-07-14 psvemmc v2.1: added EEPROM and GND pad
2018-07-27 psvemmc: v3.0 design with USB protection and clock buffering
2018-07-27 psvsd: moved bom to psvsd directory
2018-08-10 Tent vias for psvemmc
2018-08-12 psvemmc v3.1: fixed wrong pin ordering on clk buffer added pin 1 indicator to components missing them added title/value for sch in buffer components
2018-08-19 psvemmc: Wrong part number in BOM (doh)
2018-12-08 Added Mouser Part number
2019-01-17 Update bom_psvemmc_v30.csv
    Updated part list
2019-01-17 Remove white space

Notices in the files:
parts and their libraries:
NXP_60_26022015: This library may be distributed and adapted freely for any purpose, as long as NXP is credited and any new creation is licensed under the same terms.
